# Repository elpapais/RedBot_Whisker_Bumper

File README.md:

RedBot Whisker Bumper
==================

Wire switch bumper for the RedBot

[  
*RedBot Whisker Bumper*](https://www.sparkfun.com/products/11999)

Design files for the [RedBot Whisker Bumper Sensor](https://www.sparkfun.com/products/11999).

Repository Contents
-------------------

* **/hardware** - Eagle PCB layout files
* **/Production Files** - Files to support SparkFun production

License Information
-------------------

All contents of this repository are released under [Creative Commons Share-alike 3.0](http://creativecommons.org/licenses/by-sa/3.0/).

Authors: Mike Hord @ SparkFun Electonics

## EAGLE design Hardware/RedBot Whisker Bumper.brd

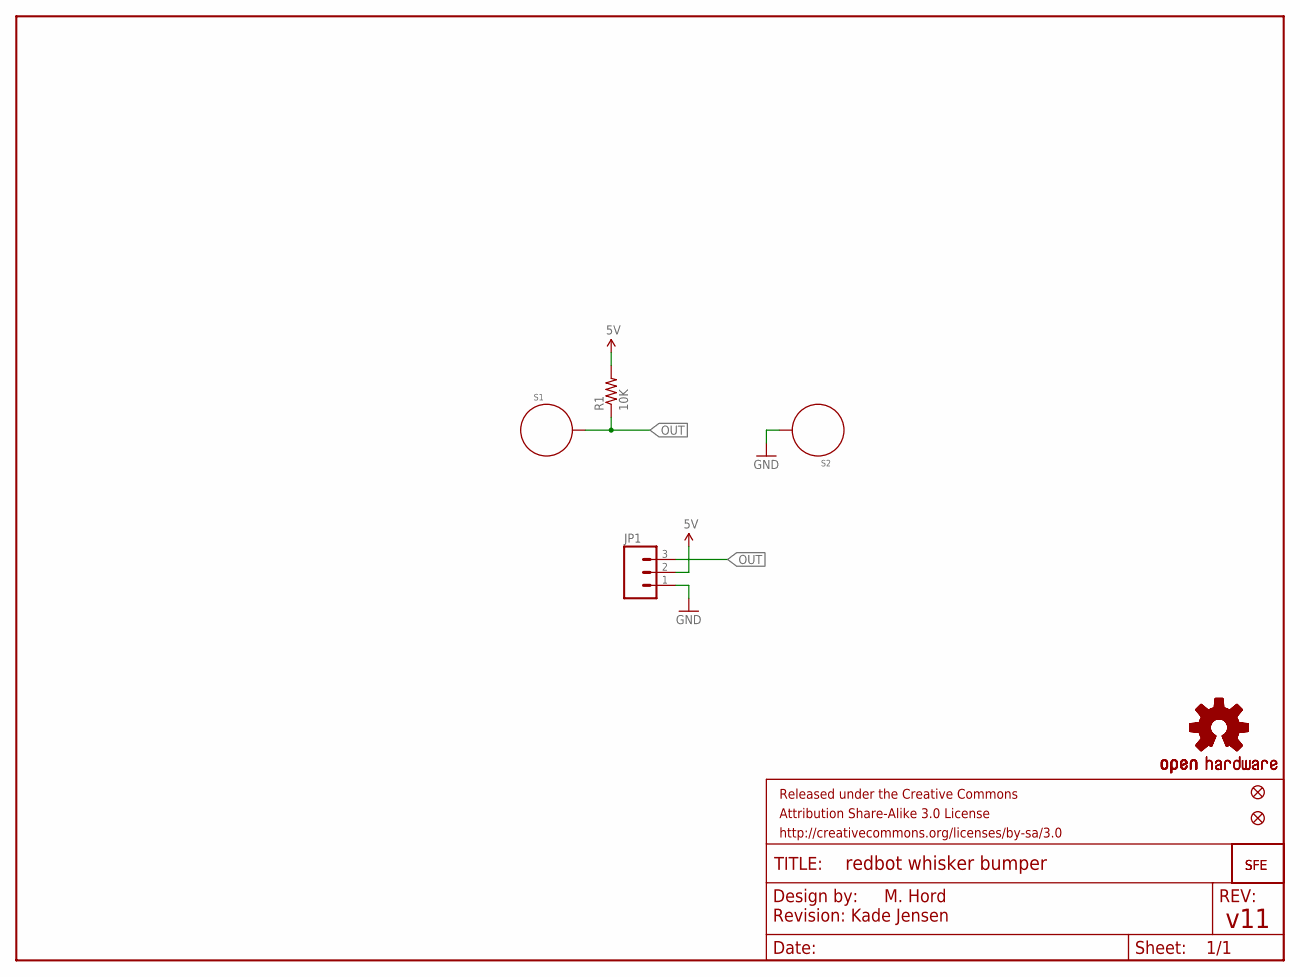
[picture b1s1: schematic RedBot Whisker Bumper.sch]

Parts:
FID1, FID2: FIDUCIALUFIDUCIAL; MICRO-FIDUCIAL
FRAME1: FRAME-LETTER; CREATIVE_COMMONS
JP1: M03SMD_RA_MALE_POST; 1X03_SMD_RA_MALE_POST
LOGO1, LOGO3: OSHW-LOGOS; OSHW-LOGO-S
LOGO2, LOGO4: LOGO-SFESK; SFE-LOGO-FLAME
R1: 10K; 0603-RES
S1, S2: STANDOFF_ELECTRICAL; STANDOFF-ELECTRICAL

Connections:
5V: JP1.2, R1.2
GND: JP1.1, S2.P1
OUT: JP1.3, R1.1, S1.P1

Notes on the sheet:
M. Hord
v11
Revision: Kade Jensen

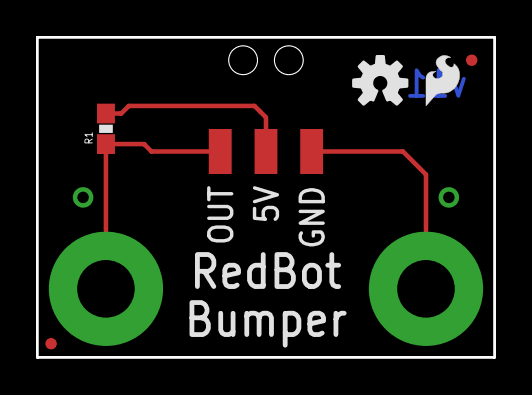
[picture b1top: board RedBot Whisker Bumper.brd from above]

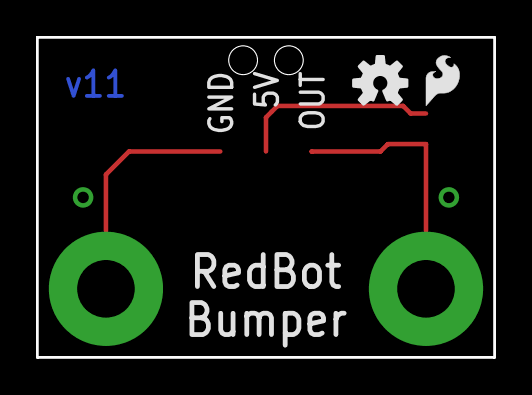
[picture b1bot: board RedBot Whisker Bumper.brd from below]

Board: 2 copper layers, 25.4 x 17.8 mm, 11 parts (2 on the bottom side), 3 nets.

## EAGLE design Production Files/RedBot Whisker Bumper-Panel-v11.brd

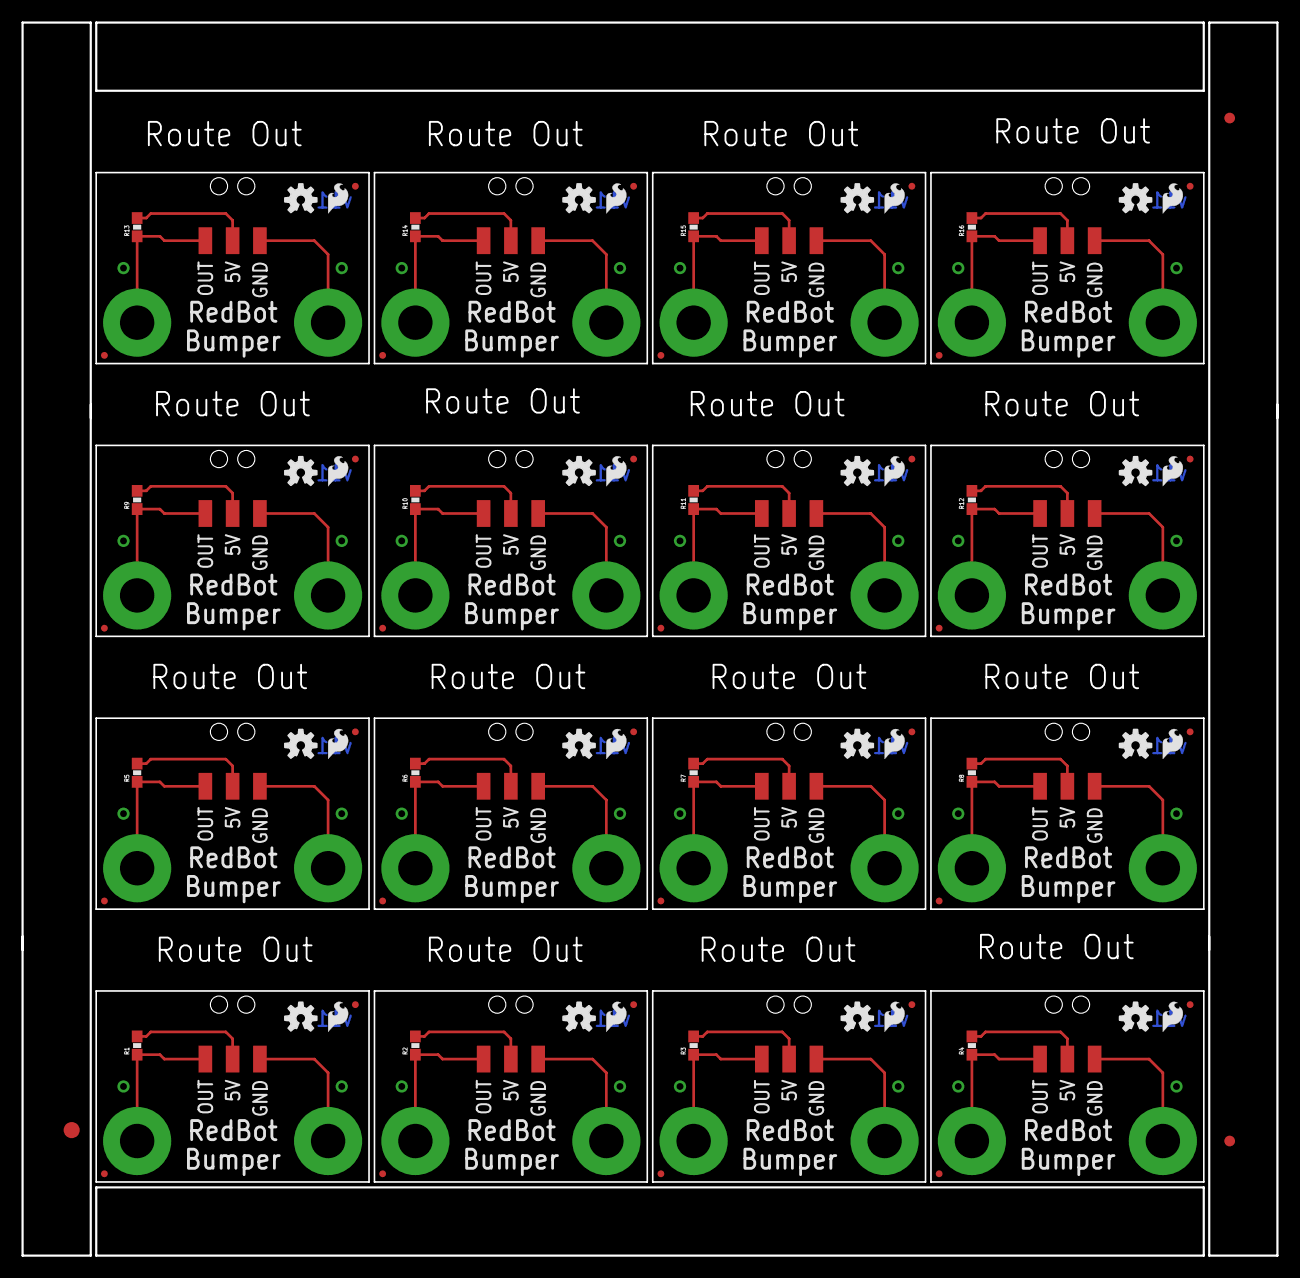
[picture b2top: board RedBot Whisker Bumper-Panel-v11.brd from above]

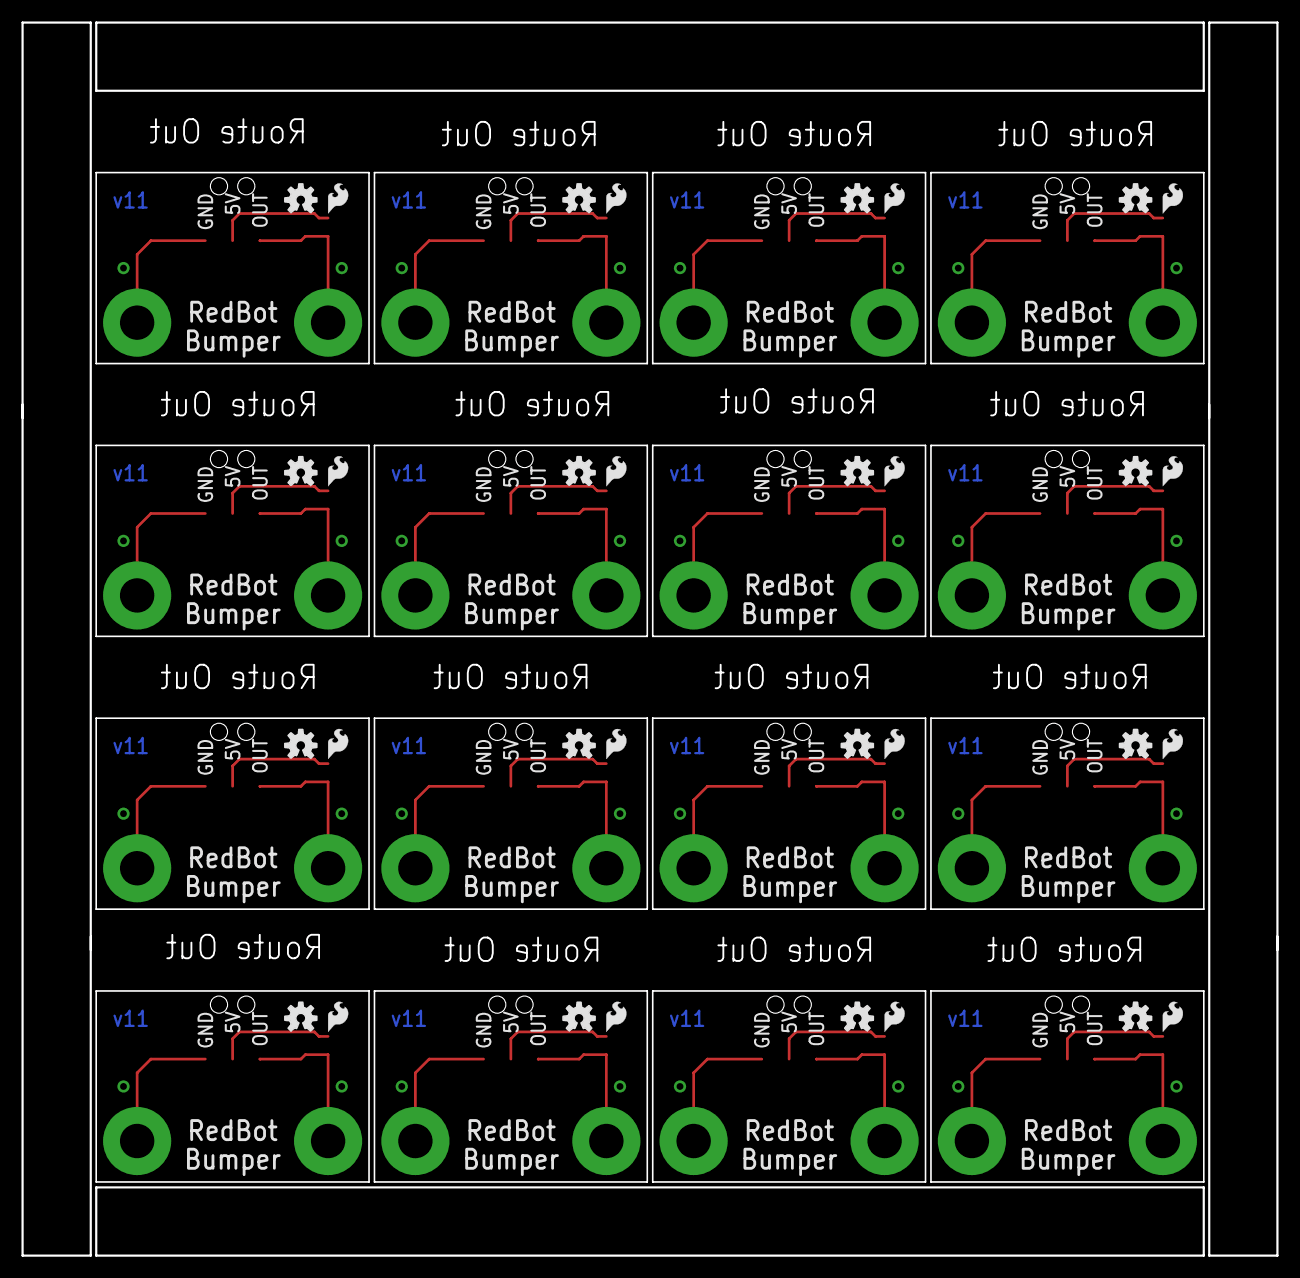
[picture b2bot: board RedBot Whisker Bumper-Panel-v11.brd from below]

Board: 2 copper layers, 116.8 x 114.8 mm, 163 parts (32 on the bottom side), 48 nets.

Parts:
E$1: FIDUCIAL-1.5X3
E$4, E$5: FIDUCIAL-1X2
FID1, FID2, FID3, FID4, FID5, FID6, FID7, FID8, FID9, FID10, FID11, FID12, FID13, FID14, FID15, FID16, FID17, FID18, FID19, FID20, FID21, FID22, FID23, FID24, FID25, FID26, FID27, FID28, FID29, FID30, FID31, FID32: FIDUCIALUFIDUCIAL; MICRO-FIDUCIAL
JP1, JP2, JP3, JP4, JP5, JP6, JP7, JP8, JP9, JP10, JP11, JP12, JP13, JP14, JP15, JP16: 1X03_SMD_RA_MALE_POST
LOGO1, LOGO3, LOGO5, LOGO7, LOGO9, LOGO11, LOGO13, LOGO15, LOGO17, LOGO19, LOGO21, LOGO23, LOGO25, LOGO27, LOGO29, LOGO31, LOGO33, LOGO35, LOGO37, LOGO39, LOGO41, LOGO43, LOGO45, LOGO47, LOGO49, LOGO51, LOGO53, LOGO55, LOGO57, LOGO59, LOGO61, LOGO63: OSHW-LOGOS; OSHW-LOGO-S
LOGO2, LOGO4, LOGO6, LOGO8, LOGO10, LOGO12, LOGO14, LOGO16, LOGO18, LOGO20, LOGO22, LOGO24, LOGO26, LOGO28, LOGO30, LOGO32, LOGO34, LOGO36, LOGO38, LOGO40, LOGO42, LOGO44, LOGO46, LOGO48, LOGO50, LOGO52, LOGO54, LOGO56, LOGO58, LOGO60, LOGO62, LOGO64: LOGO-SFESK; SFE-LOGO-FLAME
R1, R2, R3, R4, R5, R6, R7, R8, R9, R10, R11, R12, R13, R14, R15, R16: 10K; 0603-RES
S1, S2, S3, S4, S5, S6, S7, S8, S9, S10, S11, S12, S13, S14, S15, S16, S17, S18, S19, S20, S21, S22, S23, S24, S25, S26, S27, S28, S29, S30, S31, S32: STANDOFF_ELECTRICAL; STANDOFF-ELECTRICAL

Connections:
5V: JP1.2, R1.2
5V1: JP2.2, R2.2
5V2: JP3.2, R3.2
5V3: JP4.2, R4.2
5V4: JP5.2, R5.2
5V5: JP6.2, R6.2
5V6: JP7.2, R7.2
5V7: JP8.2, R8.2
5V8: JP9.2, R9.2
5V9: JP10.2, R10.2
5V10: JP11.2, R11.2
5V11: JP12.2, R12.2
5V12: JP13.2, R13.2
5V13: JP14.2, R14.2
5V14: JP15.2, R15.2
5V15: JP16.2, R16.2
GND: JP1.1, S2.P1
GND1: JP2.1, S4.P1
GND2: JP3.1, S6.P1
GND3: JP4.1, S8.P1
GND4: JP5.1, S10.P1
GND5: JP6.1, S12.P1
GND6: JP7.1, S14.P1
GND7: JP8.1, S16.P1
GND8: JP9.1, S18.P1
GND9: JP10.1, S20.P1
GND10: JP11.1, S22.P1
GND11: JP12.1, S24.P1
GND12: JP13.1, S26.P1
GND13: JP14.1, S28.P1
GND14: JP15.1, S30.P1
GND15: JP16.1, S32.P1
OUT: JP1.3, R1.1, S1.P1
OUT1: JP2.3, R2.1, S3.P1
OUT2: JP3.3, R3.1, S5.P1
OUT3: JP4.3, R4.1, S7.P1
OUT4: JP5.3, R5.1, S9.P1
OUT5: JP6.3, R6.1, S11.P1
OUT6: JP7.3, R7.1, S13.P1
OUT7: JP8.3, R8.1, S15.P1
OUT8: JP9.3, R9.1, S17.P1
OUT9: JP10.3, R10.1, S19.P1
OUT10: JP11.3, R11.1, S21.P1
OUT11: JP12.3, R12.1, S23.P1
OUT12: JP13.3, R13.1, S25.P1
OUT13: JP14.3, R14.1, S27.P1
OUT14: JP15.3, R15.1, S29.P1
OUT15: JP16.3, R16.1, S31.P1

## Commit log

2013-07-24 Initial commit, v10 for release
2013-07-24 Renamed files to match repo
2013-07-24 Removed old files.
2013-07-25 Production Readied
2013-12-04 QC Revision
    Changes:
    1.) New 3-pin SMD header footprints w/ bosses
    2.) Moved R1 position and routing for better reflow
2014-01-30 Silk fix and new dru
    Moved bottom silk pin labels closer to board edge and used updated
    Sparkfun 2 layer dru.
2014-01-30 Created Panel v11

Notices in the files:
parts and their libraries:
SparkFun-Aesthetics: Licensing: CC v3.0 Share-Alike You are welcome to use this library for commercial purposes.
SparkFun-Aesthetics: Released under the Creative Commons Attribution Share-Alike 3.0 License
SparkFun-Aesthetics: Released under the Creative Commons
